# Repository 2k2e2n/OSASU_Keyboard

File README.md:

# OSASU-Keyboard（仮）
キーボードの回路データを共有するリポジトリです。

### Author
takeishi, wataken
### Tools
- kicad 9.0.6

### Schematic

<!-- kicadiff:preview:start -->
## PCB Preview

<!-- kicadiff:preview:end -->

<!-- kicadiff:viewer:start -->
## 🔍 [View interactive PCB/schematic diff](https://2k2e2n.github.io/OSASU_Keyboard/)
<!-- kicadiff:viewer:end -->

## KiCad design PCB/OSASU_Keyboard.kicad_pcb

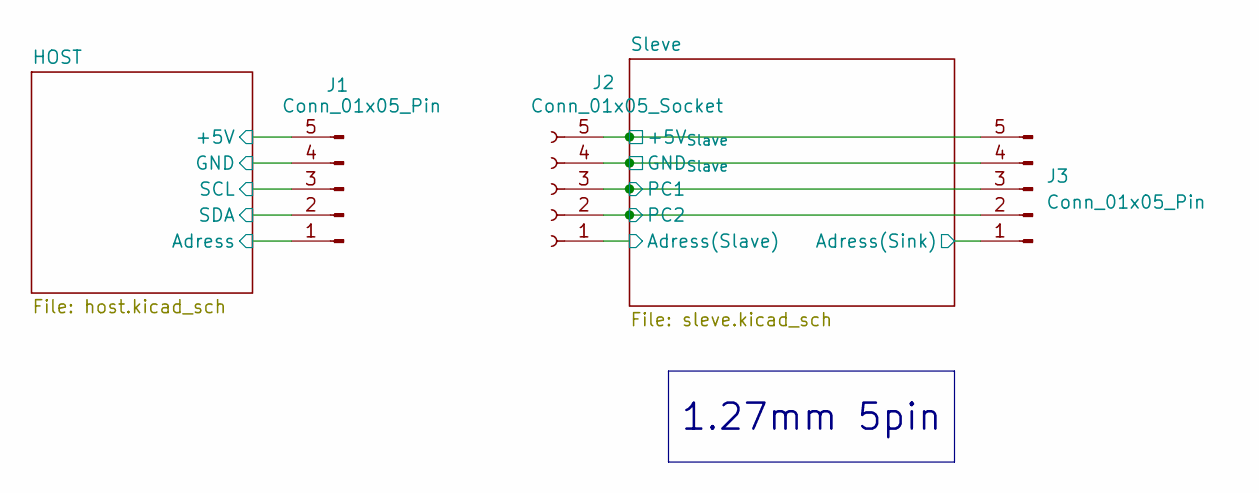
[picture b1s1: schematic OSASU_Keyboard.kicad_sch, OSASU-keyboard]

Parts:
J1, J3: Conn_01x05_Pin; PinHeader_1x05_P1.27mm_Horizontal_SMD(inversed)
J2: Conn_01x05_Socket; PinHeader_1x05_P1.27mm_Horizontal_SMD

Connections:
+5V: J1.5; also elsewhere on the board
+5V_{Slave}: J2.5, J3.5; also elsewhere on the board
/HOST/Adress_{(Source)} ⇒ Adress_{(Sink)}: J1.1; also elsewhere on the board
/HOST/SCL_{(CH552T)} = SCL_{(CH32V003)}: J1.3; also elsewhere on the board
/HOST/SDA_{(CH552T)} = SDA_{(CH32V003)}: J1.2; also elsewhere on the board
/Sleve/Adress(Sink): J3.1; also elsewhere on the board
/Sleve/Adress(Slave): J2.1; also elsewhere on the board
/Sleve/PC1: J2.3, J3.3; also elsewhere on the board
/Sleve/PC2: J2.2, J3.2; also elsewhere on the board
GND: J1.4; also elsewhere on the board
GND_{Slave}: J2.4, J3.4; also elsewhere on the board

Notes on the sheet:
1.27mm 5pin

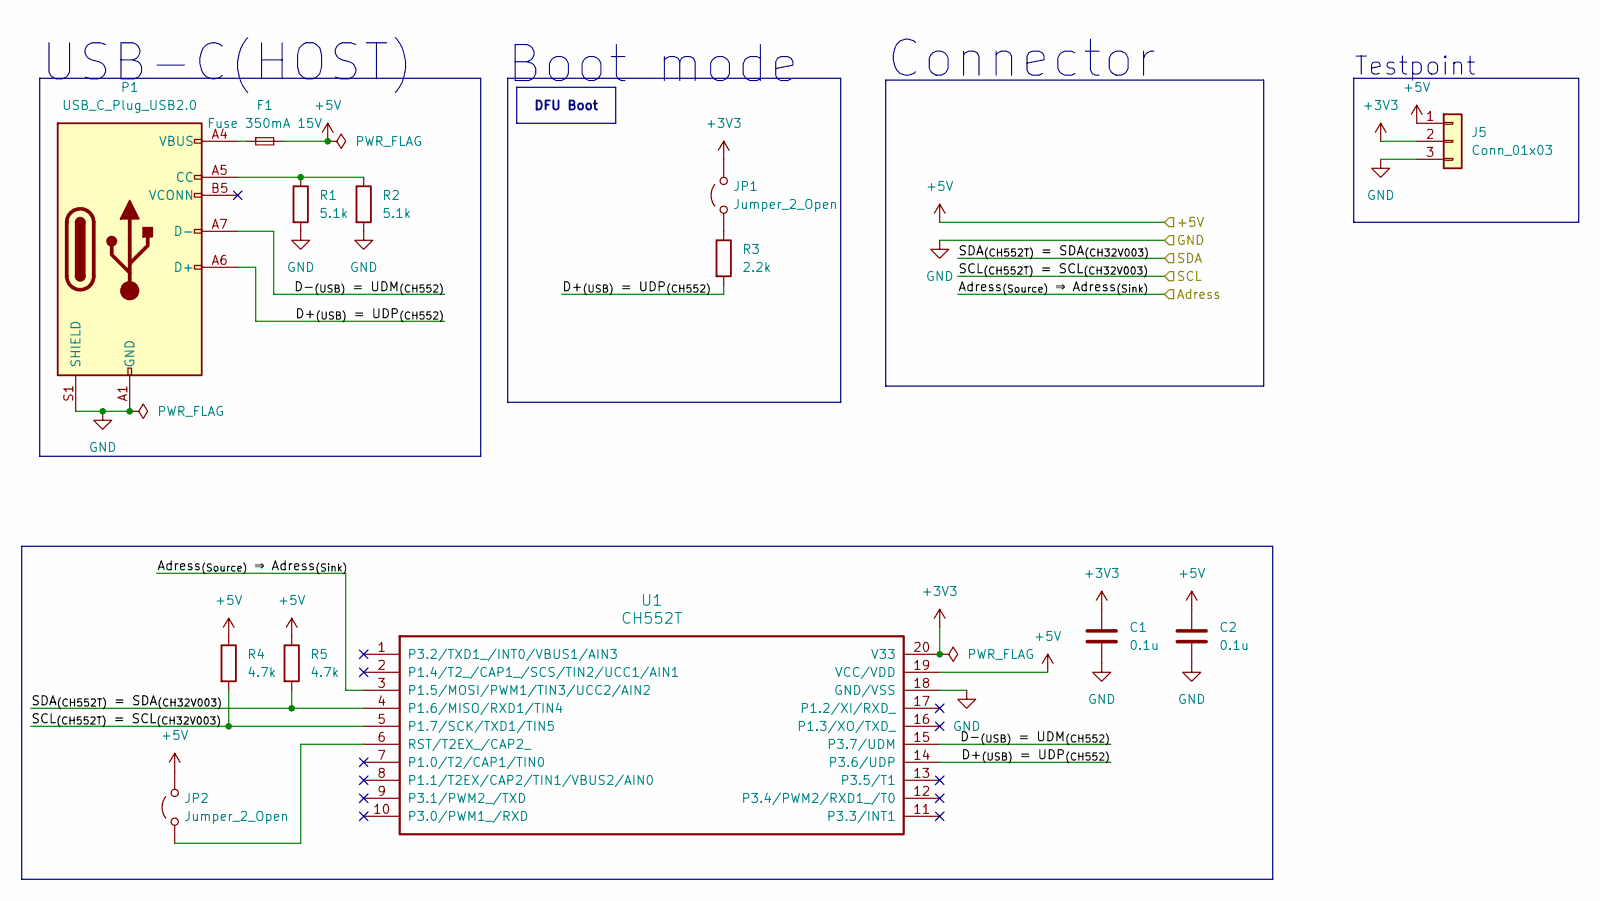
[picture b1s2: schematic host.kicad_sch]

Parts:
C1, C2: 0.1u; C_0603_1608Metric_Pad1.08x0.95mm_HandSolder
F1: Fuse 350mA 15V; Fuse_0603_1608Metric
J5: Conn_01x03; PinHeader_1x03_P2.54mm_Vertical
JP1, JP2: Jumper_2_Open; SolderJumper-2_P1.3mm_Open_RoundedPad1.0x1.5mm
P1: USB_C_Plug_USB2.0; USB_C_Receptacle_GCT_USB4105-xx-A_16P_TopMnt_Horizontal
R1, R2: 5.1k; R_0603_1608Metric_Pad0.98x0.95mm_HandSolder
R3: 2.2k; R_0603_1608Metric_Pad0.98x0.95mm_HandSolder
R4, R5: 4.7k; R_0603_1608Metric_Pad0.98x0.95mm_HandSolder
U1: CH552T; TSSOP-20_4.4x6.5mm_P0.65mm

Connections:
+3V3: C1.1, J5.2, JP1.2 (B), U1.20 (V33)
+5V: C2.1, F1.2, J5.1, JP2.2 (B), R4.1, R5.1, U1.19 (VCC/VDD); also elsewhere on the board
/HOST/Adress_{(Source)} ⇒ Adress_{(Sink)}: U1.3 (P1.5/MOSI/PWM1/TIN3/UCC2/AIN2); also elsewhere on the board
/HOST/D+_{(USB)} = UDP_{(CH552)}: P1.A6 (D+), R3.2, U1.14 (P3.6/UDP)
/HOST/D-_{(USB)} = UDM_{(CH552)}: P1.A7 (D-), U1.15 (P3.7/UDM)
/HOST/SCL_{(CH552T)} = SCL_{(CH32V003)}: R4.2, U1.5 (P1.7/SCK/TXD1/TIN5); also elsewhere on the board
/HOST/SDA_{(CH552T)} = SDA_{(CH32V003)}: R5.2, U1.4 (P1.6/MISO/RXD1/TIN4); also elsewhere on the board
GND: C1.2, C2.2, J5.3, P1.A1 (GND), P1.A12 (GND), P1.B1 (GND), P1.B12 (GND), P1.S1 (SHIELD), R1.2, R2.2, U1.18 (GND/VSS); also elsewhere on the board
unnamed: F1.1, P1.A4 (VBUS), P1.A9 (VBUS), P1.B4 (VBUS), P1.B9 (VBUS)
unnamed: JP1.1 (A), R3.1
unnamed: JP2.1 (A), U1.6 (RST/T2EX_/CAP2_)
unnamed: P1.A5 (CC), R1.1, R2.1

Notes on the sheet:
Testpoint
Boot mode
USB-C(HOST)
Connector
DFU Boot

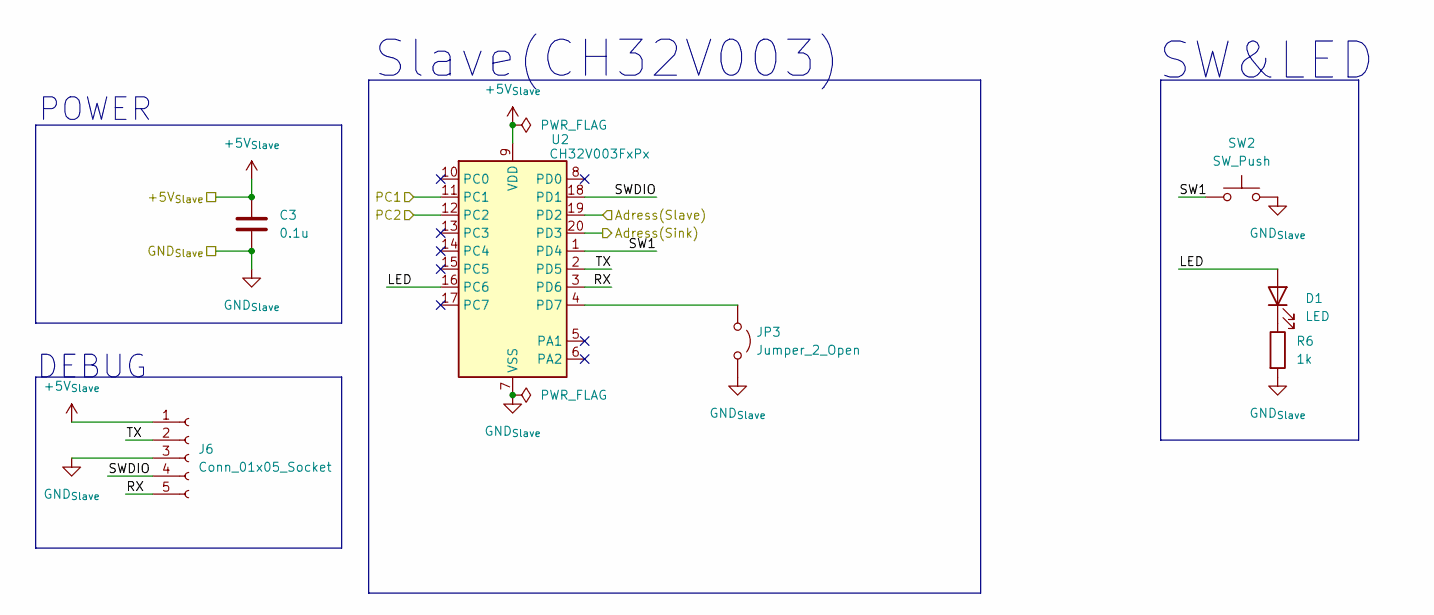
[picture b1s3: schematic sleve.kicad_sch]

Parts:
C3: 0.1u; C_0603_1608Metric_Pad1.08x0.95mm_HandSolder
D1: LED; D_LED_5730
J6: Conn_01x05_Socket; PinHeader_1x05_P2.54mm_Vertical
JP3: Jumper_2_Open; SolderJumper-2_P1.3mm_Open_RoundedPad1.0x1.5mm
R6: 1k; R_0603_1608Metric_Pad0.98x0.95mm_HandSolder
SW2: SW_Push; SW_Cherry_MX_1.00u_PCB
U2: CH32V003FxPx; TSSOP-20_4.4x6.5mm_P0.65mm

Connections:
+5V_{Slave}: C3.1, J6.1, U2.9 (VDD); also elsewhere on the board
/Sleve/Adress(Sink): U2.20 (PD3); also elsewhere on the board
/Sleve/Adress(Slave): U2.19 (PD2); also elsewhere on the board
/Sleve/LED: D1.2 (A), U2.16 (PC6)
/Sleve/PC1: U2.11 (PC1); also elsewhere on the board
/Sleve/PC2: U2.12 (PC2); also elsewhere on the board
/Sleve/RX: J6.5, U2.3 (PD6)
/Sleve/SW1: SW2.1, U2.1 (PD4)
/Sleve/SWDIO: J6.4, U2.18 (PD1)
/Sleve/TX: J6.2, U2.2 (PD5)
GND_{Slave}: C3.2, J6.3, JP3.2 (B), R6.2, SW2.2, U2.7 (VSS); also elsewhere on the board
unnamed: D1.1 (K), R6.1
unnamed: JP3.1 (A), U2.4 (PD7)

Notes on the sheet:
DEBUG
POWER
Slave(CH32V003)
SW&LED

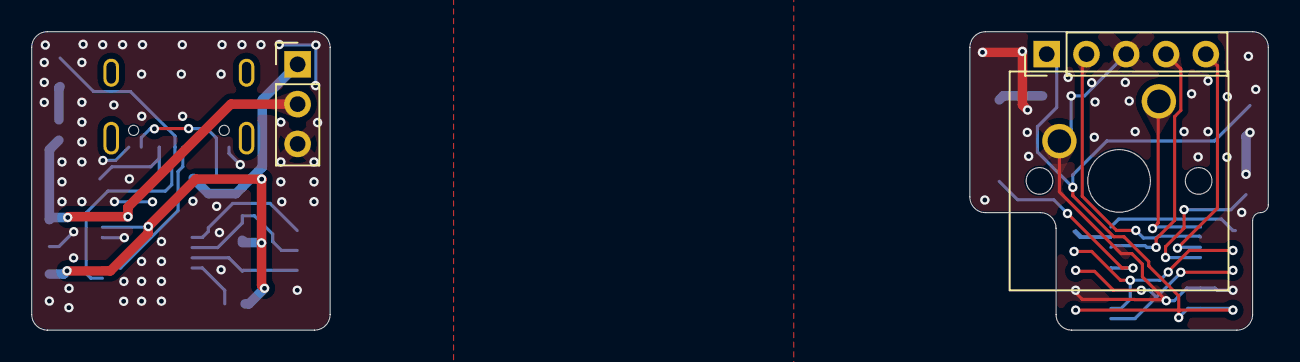
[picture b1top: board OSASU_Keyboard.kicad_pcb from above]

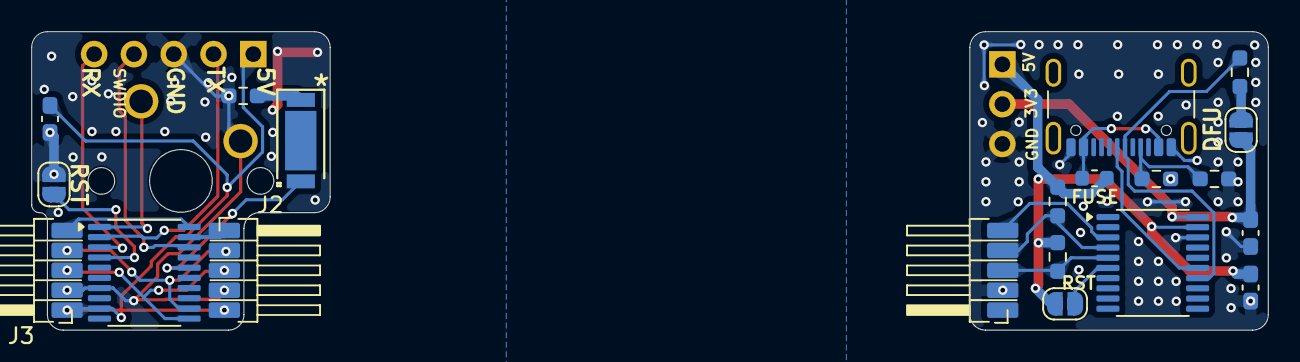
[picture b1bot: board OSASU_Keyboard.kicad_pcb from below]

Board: 2 copper layers, 78.9 x 19.0 mm, 23 parts (20 on the bottom side), 25 nets.

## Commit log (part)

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2025-12-22 Add initial README with project details
2025-12-22 update schematic
2026-05-10 schematicを更新
2026-05-10 PCB更新
2026-05-11 基盤更新
2026-05-12 add workflow
2026-05-12 ccommit
2026-06-13 基盤設計
